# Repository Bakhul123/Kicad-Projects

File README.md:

# Kicad-Projects
this is My Kicad Project Repositories

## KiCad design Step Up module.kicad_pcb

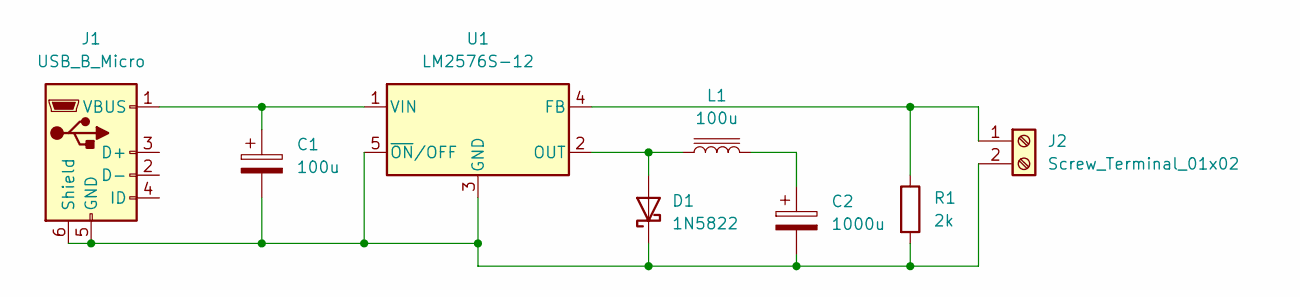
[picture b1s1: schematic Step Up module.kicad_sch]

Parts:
C1: 100u; CP_Elec_10x12.6
C2: 1000u; CP_Elec_10x12.6
D1: 1N5822; D_DO-201AD_P15.24mm_Horizontal
J1: USB_B_Micro; USB_Micro-B_Molex-105017-0001
J2: Screw_Terminal_01x02; TerminalBlock_Altech_AK300-2_P5.00mm
L1: 100u; L_Coilcraft_XAL1010-XXX
R1: 2k; R_2512_6332Metric_Pad1.40x3.35mm_HandSolder
U1: LM2576S-12; TO-263-5_TabPin3

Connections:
unnamed: C2.1, L1.2
unnamed: D1.2 (A), L1.1, U1.2 (OUT)
unnamed: C1.2, C2.2, D1.1 (K), J1.5 (GND), J1.6 (Shield), J2.2, R1.2, U1.3 (GND), U1.5 (~ON/OFF)
unnamed: C1.1, J1.1 (VBUS), U1.1 (VIN)
unnamed: J2.1, R1.1, U1.4 (FB)

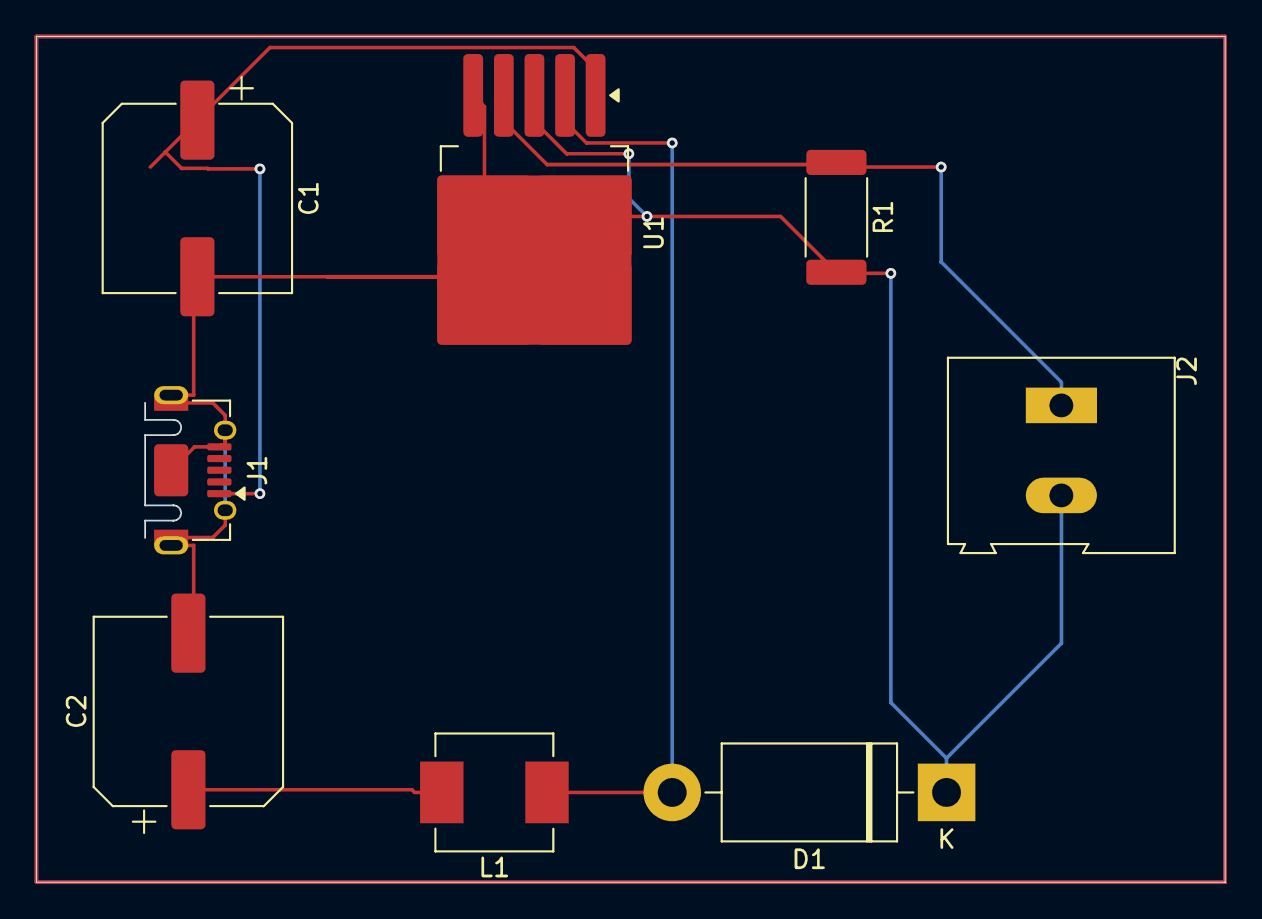
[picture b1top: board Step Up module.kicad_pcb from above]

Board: 2 copper layers, 66.0 x 46.9 mm, 8 parts (0 on the bottom side), 5 nets.
